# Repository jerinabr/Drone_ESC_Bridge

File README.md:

# Drone_ESC_Bridge
## Description
This board is intended to act as a bridge between the Nvidia Jetson and the 4-in-1 ESC on the ADP drone[^1]

It recieves motor speeds and other commands from the Jetson over the SPI interface and outputs motor speeds to the ESC over PWM

It also monitors the LiPo voltage and can report it back to the Jetson over the SPI interface

The board receives 5V power from an off-board buck converter which is used to power both the microcontroller (Seeed XIAO SAMD21) and the Jetson

[^1]: Firmware for the Jetson and Seeed XIAO can be found [here](https://github.com/LarsGart/Autonomous-Drone-Platform)

## BOM
| Reference         | Value                 | Footprint                                                    | Qty | DigiKey Part Number      |
| ----------------- | --------------------- | ------------------------------------------------------------ | --- | ------------------------ |
| C1,C2,C4,C6,C7,C8 | 0.1u                  | Capacitor_SMD:C_0603_1608Metric_Pad1.08x0.95mm_HandSolder    | 6   | 311-1088-1-ND            |
| C3                | 1u                    | Capacitor_SMD:C_0603_1608Metric_Pad1.08x0.95mm_HandSolder    | 1   | 311-1446-1-ND            |
| C5                | 22u                   | Capacitor_SMD:CP_Elec_6.3x5.8                                | 1   | PCE3811CT-ND             |
| ESC1              | Conn_01x08            | Connector_JST:JST_SH_BM08B-SRSS-TB_1x08-1MP_P1.00mm_Vertical | 1   | 455-BM08B-SRSS-TBCT-ND   |
| ESC_DEBUG1        | Conn_01x06            | Connector_PinHeader_2.54mm:PinHeader_2x03_P2.54mm_Vertical   | 1   | 2057-PH2-06-UA-ND        |
| JETSON_PWR1       | Conn_02x02_Top_Bottom | Connector_PinHeader_2.54mm:PinHeader_2x02_P2.54mm_Vertical   | 1   | 2057-PH2-04-UA-ND        |
| Q1                | Si2318CDS             | Package_TO_SOT_SMD:SOT-23-3                                  | 1   | SI2318CDS-T1-GE3CT-ND    |
| R1                | 10m                   | Resistor_SMD:R_2010_5025Metric_Pad1.40x2.65mm_HandSolder     | 1   | 13-PE2010FKE070R01LCT-ND |
| R2                | 100                   | Resistor_SMD:R_0603_1608Metric_Pad0.98x0.95mm_HandSolder     | 1   | 311-100HRCT-ND           |
| R3                | 33k                   | Resistor_SMD:R_0603_1608Metric_Pad0.98x0.95mm_HandSolder     | 1   | 311-33.0KHRTR-ND         |
| R4                | 8.2k                  | Resistor_SMD:R_0603_1608Metric_Pad0.98x0.95mm_HandSolder     | 1   | 311-8.2KGRTR-ND          |
| SPI1,VBUCK1       | Conn_01x04            | Connector_PinHeader_2.54mm:PinHeader_2x02_P2.54mm_Vertical   | 2   | 2057-PH2-04-UA-ND        |
| U1                | LMP8640               | Package_TO_SOT_SMD:SOT-23-6                                  | 1   | 296-48927-1-ND           |
| U2                | LM5050-1              | Package_TO_SOT_SMD:TSOT-23-6                                 | 1   | 296-46427-1-ND           |
| XIAO_L1,XIAO_R1   | Conn_01x07            | Connector_PinSocket_2.54mm:PinSocket_1x07_P2.54mm_Vertical   | 2   | S7040-ND                 |

> [!NOTE]
> `JETSON_PWR1` has the same part number has `SPI1` and `VBUCK1`\
> They're separate entries because the connector footprint used in the schematic was different

## Images
### Schematic

### Top Layer

### Bottom Layer

### 3D Top View

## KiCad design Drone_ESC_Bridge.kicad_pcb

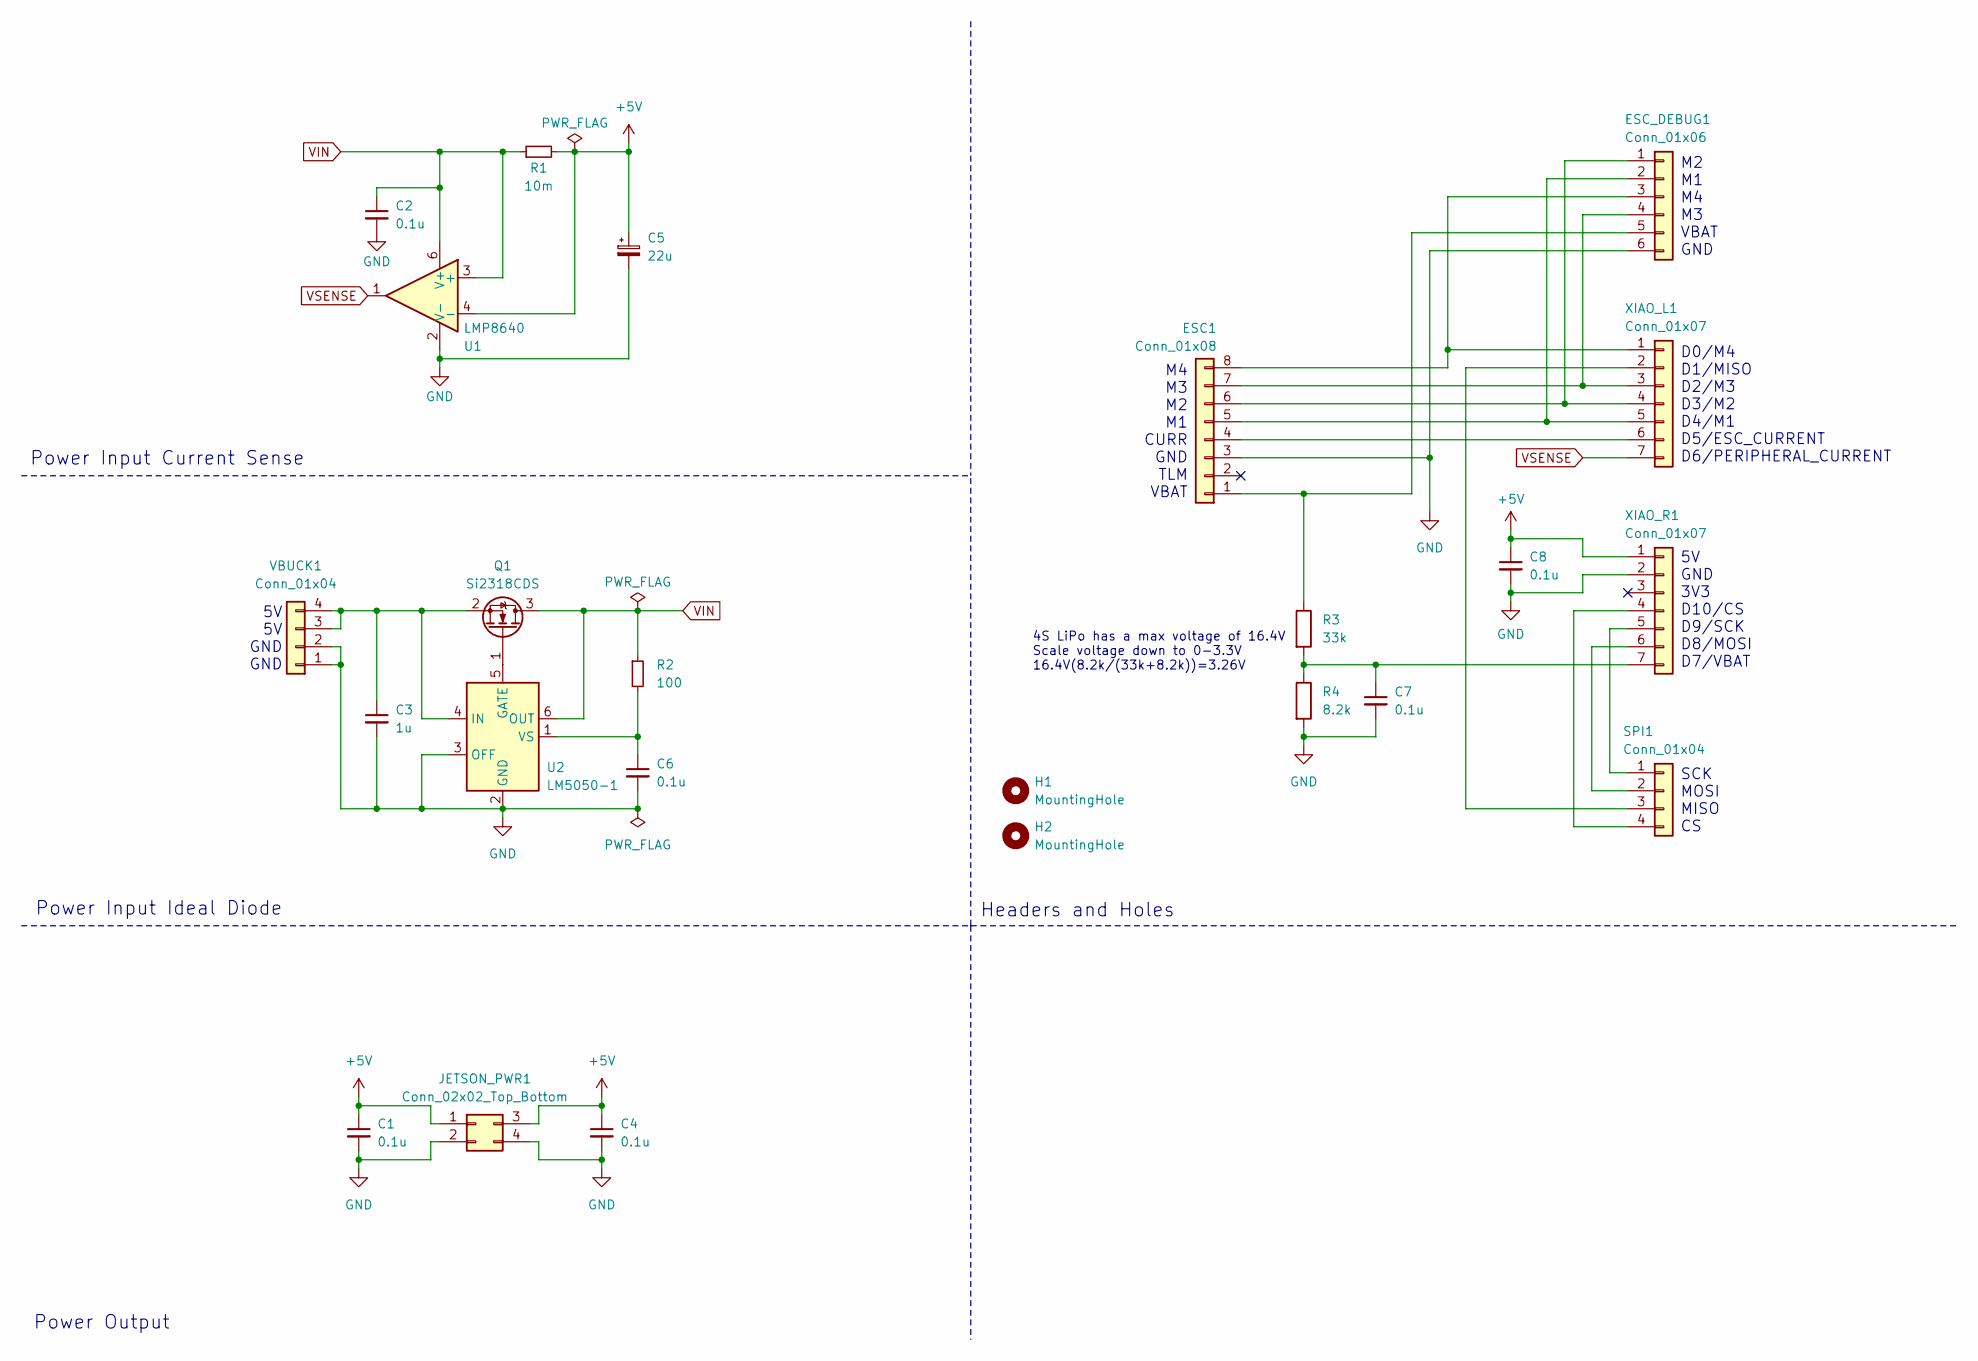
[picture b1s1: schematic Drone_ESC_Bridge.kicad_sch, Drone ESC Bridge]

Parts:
C1, C2, C4, C6, C7, C8: 0.1u; C_0603_1608Metric_Pad1.08x0.95mm_HandSolder; Part Number 311-1088-1-ND
C3: 1u; C_0603_1608Metric_Pad1.08x0.95mm_HandSolder; Part Number 311-1446-1-ND
C5: 22u; CP_Elec_6.3x5.8; Part Number PCE3811CT-ND
ESC1: Conn_01x08; JST_SH_BM08B-SRSS-TB_1x08-1MP_P1.00mm_Vertical; Part Number 455-BM08B-SRSS-TBCT-ND
ESC_DEBUG1: Conn_01x06; PinHeader_2x03_P2.54mm_Vertical; Part Number 2057-PH2-06-UA-ND
H1, H2: MountingHole; MountingHole_3.2mm_M3
JETSON_PWR1: Conn_02x02_Top_Bottom; PinHeader_2x02_P2.54mm_Vertical; Part Number 2057-PH2-04-UA-ND
Q1: Si2318CDS; SOT-23-3; Part Number SI2318CDS-T1-GE3CT-ND
R1: 10m; R_2010_5025Metric_Pad1.40x2.65mm_HandSolder; Part Number 13-PE2010FKE070R01LCT-ND
R2: 100; R_0603_1608Metric_Pad0.98x0.95mm_HandSolder; Part Number 311-100HRCT-ND
R3: 33k; R_0603_1608Metric_Pad0.98x0.95mm_HandSolder
R4: 8.2k; R_0603_1608Metric_Pad0.98x0.95mm_HandSolder
SPI1: Conn_01x04; PinHeader_2x02_P2.54mm_Vertical; Part Number 2057-PH2-04-UA-ND
U1: LMP8640; SOT-23-6; Part Number 296-48927-1-ND
U2: LM5050-1; TSOT-23-6; Part Number 296-46427-1-ND
VBUCK1: Conn_01x04; PinHeader_2x02_P2.54mm_Vertical; Part Number 2057-PH2-04-UA-ND
XIAO_L1: Conn_01x07; PinSocket_1x07_P2.54mm_Vertical; Part Number S7040-ND
XIAO_R1: Conn_01x07; PinSocket_1x07_P2.54mm_Vertical; Part Number S7040-ND

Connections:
+5V: C1.1, C4.1, C5.1, C8.1, JETSON_PWR1.1, JETSON_PWR1.3, R1.2, U1.4 (-), XIAO_R1.1
GND: C1.2, C2.2, C3.2, C4.2, C5.2, C6.2, C7.2, C8.2, ESC1.3, ESC_DEBUG1.6, JETSON_PWR1.2, JETSON_PWR1.4, R4.2, U1.2 (V-), U2.2 (GND), U2.3 (OFF), VBUCK1.1, VBUCK1.2, XIAO_R1.2
unnamed: ESC1.1, ESC_DEBUG1.5, R3.1
unnamed: ESC1.4, XIAO_L1.6
unnamed: ESC1.5, ESC_DEBUG1.2, XIAO_L1.5
unnamed: ESC1.6, ESC_DEBUG1.1, XIAO_L1.4
unnamed: ESC1.7, ESC_DEBUG1.4, XIAO_L1.3
unnamed: ESC1.8, ESC_DEBUG1.3, XIAO_L1.1
unnamed: Q1.1 (G), U2.5 (GATE)
unnamed: C3.1, Q1.2 (S), U2.4 (IN), VBUCK1.3, VBUCK1.4
unnamed: SPI1.1, XIAO_R1.5
unnamed: SPI1.2, XIAO_R1.6
unnamed: SPI1.3, XIAO_L1.2
unnamed: SPI1.4, XIAO_R1.4
unnamed: C6.1, R2.2, U2.1 (VS)
unnamed: C7.1, R3.2, R4.1, XIAO_R1.7
VIN: C2.1, Q1.3 (D), R1.1, R2.1, U1.3 (+), U1.6 (V+), U2.6 (OUT)
VSENSE: U1.1, XIAO_L1.7

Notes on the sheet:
M2 M1 M4 M3 VBAT GND
Power Output
4S LiPo has a max voltage of 16.4V Scale voltage down to 0-3.3V 16.4V(8.2k/(33k+8.2k))=3.26V
5V 5V GND GND
5V GND 3V3 D10/CS D9/SCK D8/MOSI D7/VBAT
Power Input Current Sense
M4 M3 M2 M1 CURR GND TLM VBAT
Power Input Ideal Diode
D0/M4 D1/MISO D2/M3 D3/M2 D4/M1 D5/ESC_CURRENT D6/PERIPHERAL_CURRENT
Headers and Holes
SCK MOSI MISO CS

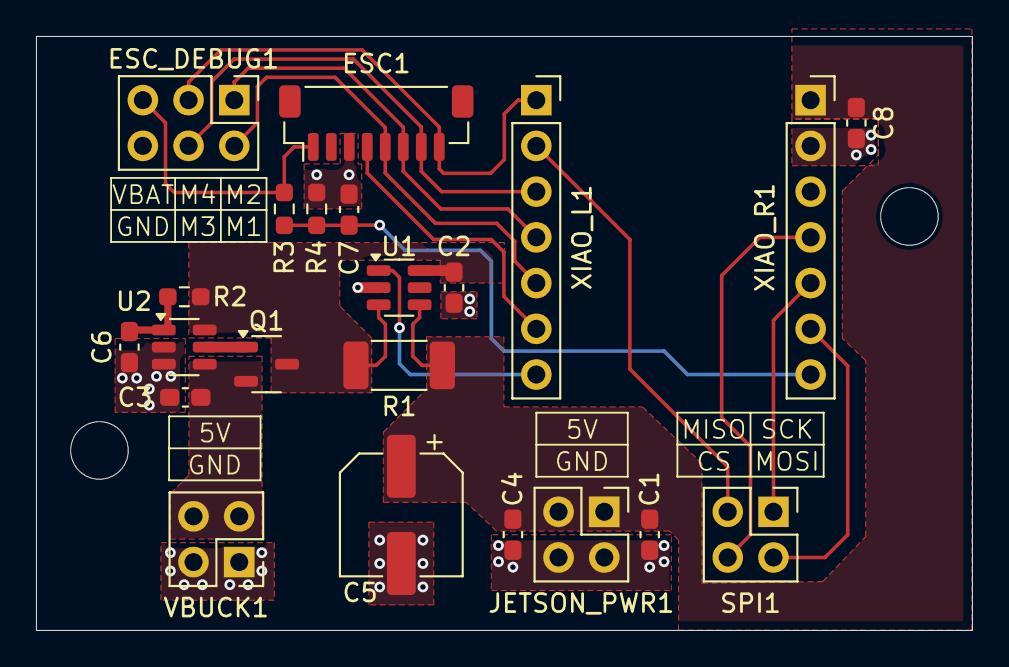
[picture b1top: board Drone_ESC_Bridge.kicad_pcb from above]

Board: 2 copper layers, 52.0 x 33.0 mm, 24 parts (0 on the bottom side), 18 nets.

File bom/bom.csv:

"Reference","Value","Footprint","Qty","Part Number"
"C1,C2,C4,C6,C7,C8","0.1u","Capacitor_SMD:C_0603_1608Metric_Pad1.08x0.95mm_HandSolder","6","311-1088-1-ND"
"C3","1u","Capacitor_SMD:C_0603_1608Metric_Pad1.08x0.95mm_HandSolder","1","311-1446-1-ND"
"C5","22u","Capacitor_SMD:CP_Elec_6.3x5.8","1","PCE3811CT-ND"
"ESC1","Conn_01x08","Connector_JST:JST_SH_BM08B-SRSS-TB_1x08-1MP_P1.00mm_Vertical","1","455-BM08B-SRSS-TBCT-ND"
"ESC_DEBUG1","Conn_01x06","Connector_PinHeader_2.54mm:PinHeader_2x03_P2.54mm_Vertical","1","2057-PH2-06-UA-ND"
"JETSON_PWR1","Conn_02x02_Top_Bottom","Connector_PinHeader_2.54mm:PinHeader_2x02_P2.54mm_Vertical","1","2057-PH2-04-UA-ND"
"Q1","Si2318CDS","Package_TO_SOT_SMD:SOT-23-3","1","SI2318CDS-T1-GE3CT-ND"
"R1","10m","Resistor_SMD:R_2010_5025Metric_Pad1.40x2.65mm_HandSolder","1","13-PE2010FKE070R01LCT-ND"
"R2","100","Resistor_SMD:R_0603_1608Metric_Pad0.98x0.95mm_HandSolder","1","311-100HRCT-ND"
"R3","33k","Resistor_SMD:R_0603_1608Metric_Pad0.98x0.95mm_HandSolder","1","311-33.0KHRTR-ND"
"R4","8.2k","Resistor_SMD:R_0603_1608Metric_Pad0.98x0.95mm_HandSolder","1","311-8.2KGRTR-ND"
"SPI1,VBUCK1","Conn_01x04","Connector_PinHeader_2.54mm:PinHeader_2x02_P2.54mm_Vertical","2","2057-PH2-04-UA-ND"
"U1","LMP8640","Package_TO_SOT_SMD:SOT-23-6","1","296-48927-1-ND"
"U2","LM5050-1","Package_TO_SOT_SMD:TSOT-23-6","1","296-46427-1-ND"
"XIAO_L1,XIAO_R1","Conn_01x07","Connector_PinSocket_2.54mm:PinSocket_1x07_P2.54mm_Vertical","2","S7040-ND"

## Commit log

2025-04-04 Initial release
2025-04-06 Initial board revision
2025-04-10 Make v in version silkscreen lowercase
2025-05-03 Update Diagram
2025-05-03 Replace telemetry with VBat sense
2025-05-03 Update gerbers
2025-05-03 Update Changelog
2025-05-04 Update images
2025-05-04 Shrink ground polygon box
2025-05-31 Add BOM and update ibom
2025-05-31 Move BOM into bom folder
